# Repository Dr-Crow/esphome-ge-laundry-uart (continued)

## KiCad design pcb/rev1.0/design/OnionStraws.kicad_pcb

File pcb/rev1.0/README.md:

# PCB Rev 1.0

Rev 1.0 is the historical one-input carrier for a generic 38-pin classic ESP32 development board and an external buck module. It added resistor positions for inverted GEA2 serial signaling. Current C3 firmware profiles do not match this board's UART pins.

[Editable source](design/) has been restored from exact public commit `87984047ee029efb83bf9947dc21818fd18e39b3` and cleaned with project-local source definitions and explicit external-supply ERC modelling. The original pin/net groups, parts, routes, positions, outline and holes are retained. Only connector silk outside the board has a physical geometry edit. Genuine KiCad 9.0.9 reports zero ERC errors/warnings after explicit faithful VCC presentation, and zero DRC/parity/unconnected findings.

Read the [native source review](validation/NATIVE-REVIEW.md), [schematic](validation/schematic.pdf), [board views](validation/views/), and [source/export proof](validation/native-kicad-9.0.9/preservation-proof.json). The [current review CAM](review-manufacturing/) is separate from the byte-preserved [original Gerber archive](manufacturing/GERBER-OnionStraws-rev1.0.zip). No supplier BOM or CPL was present in the original package; none has been invented.

This historical source cleanup does not establish electrical/appliance qualification or manufacturing readiness. Original supply, protection, supervisor, buck-module, thermal and physical gates remain open. Classic ESP32 firmware is handled separately.

[Back to the PCB revision index](../README.md)

[Standalone candidate scope and release boundaries](STANDALONE-REVIEW.md).

## Current schematic presentation

[Schematic normalization](validation/erc-normalization/integration-updates.json) resolves the former alias warnings with explicit faithful power presentation. Native KiCad 9.0.9 now reports zero errors/warnings/unconnected/parity. Original physical architecture, PCB/CAM, firmware and pin memberships remain; power/module/procurement/assembly/physical gates are still open. Earlier source/independent receipts are frozen historical evidence.

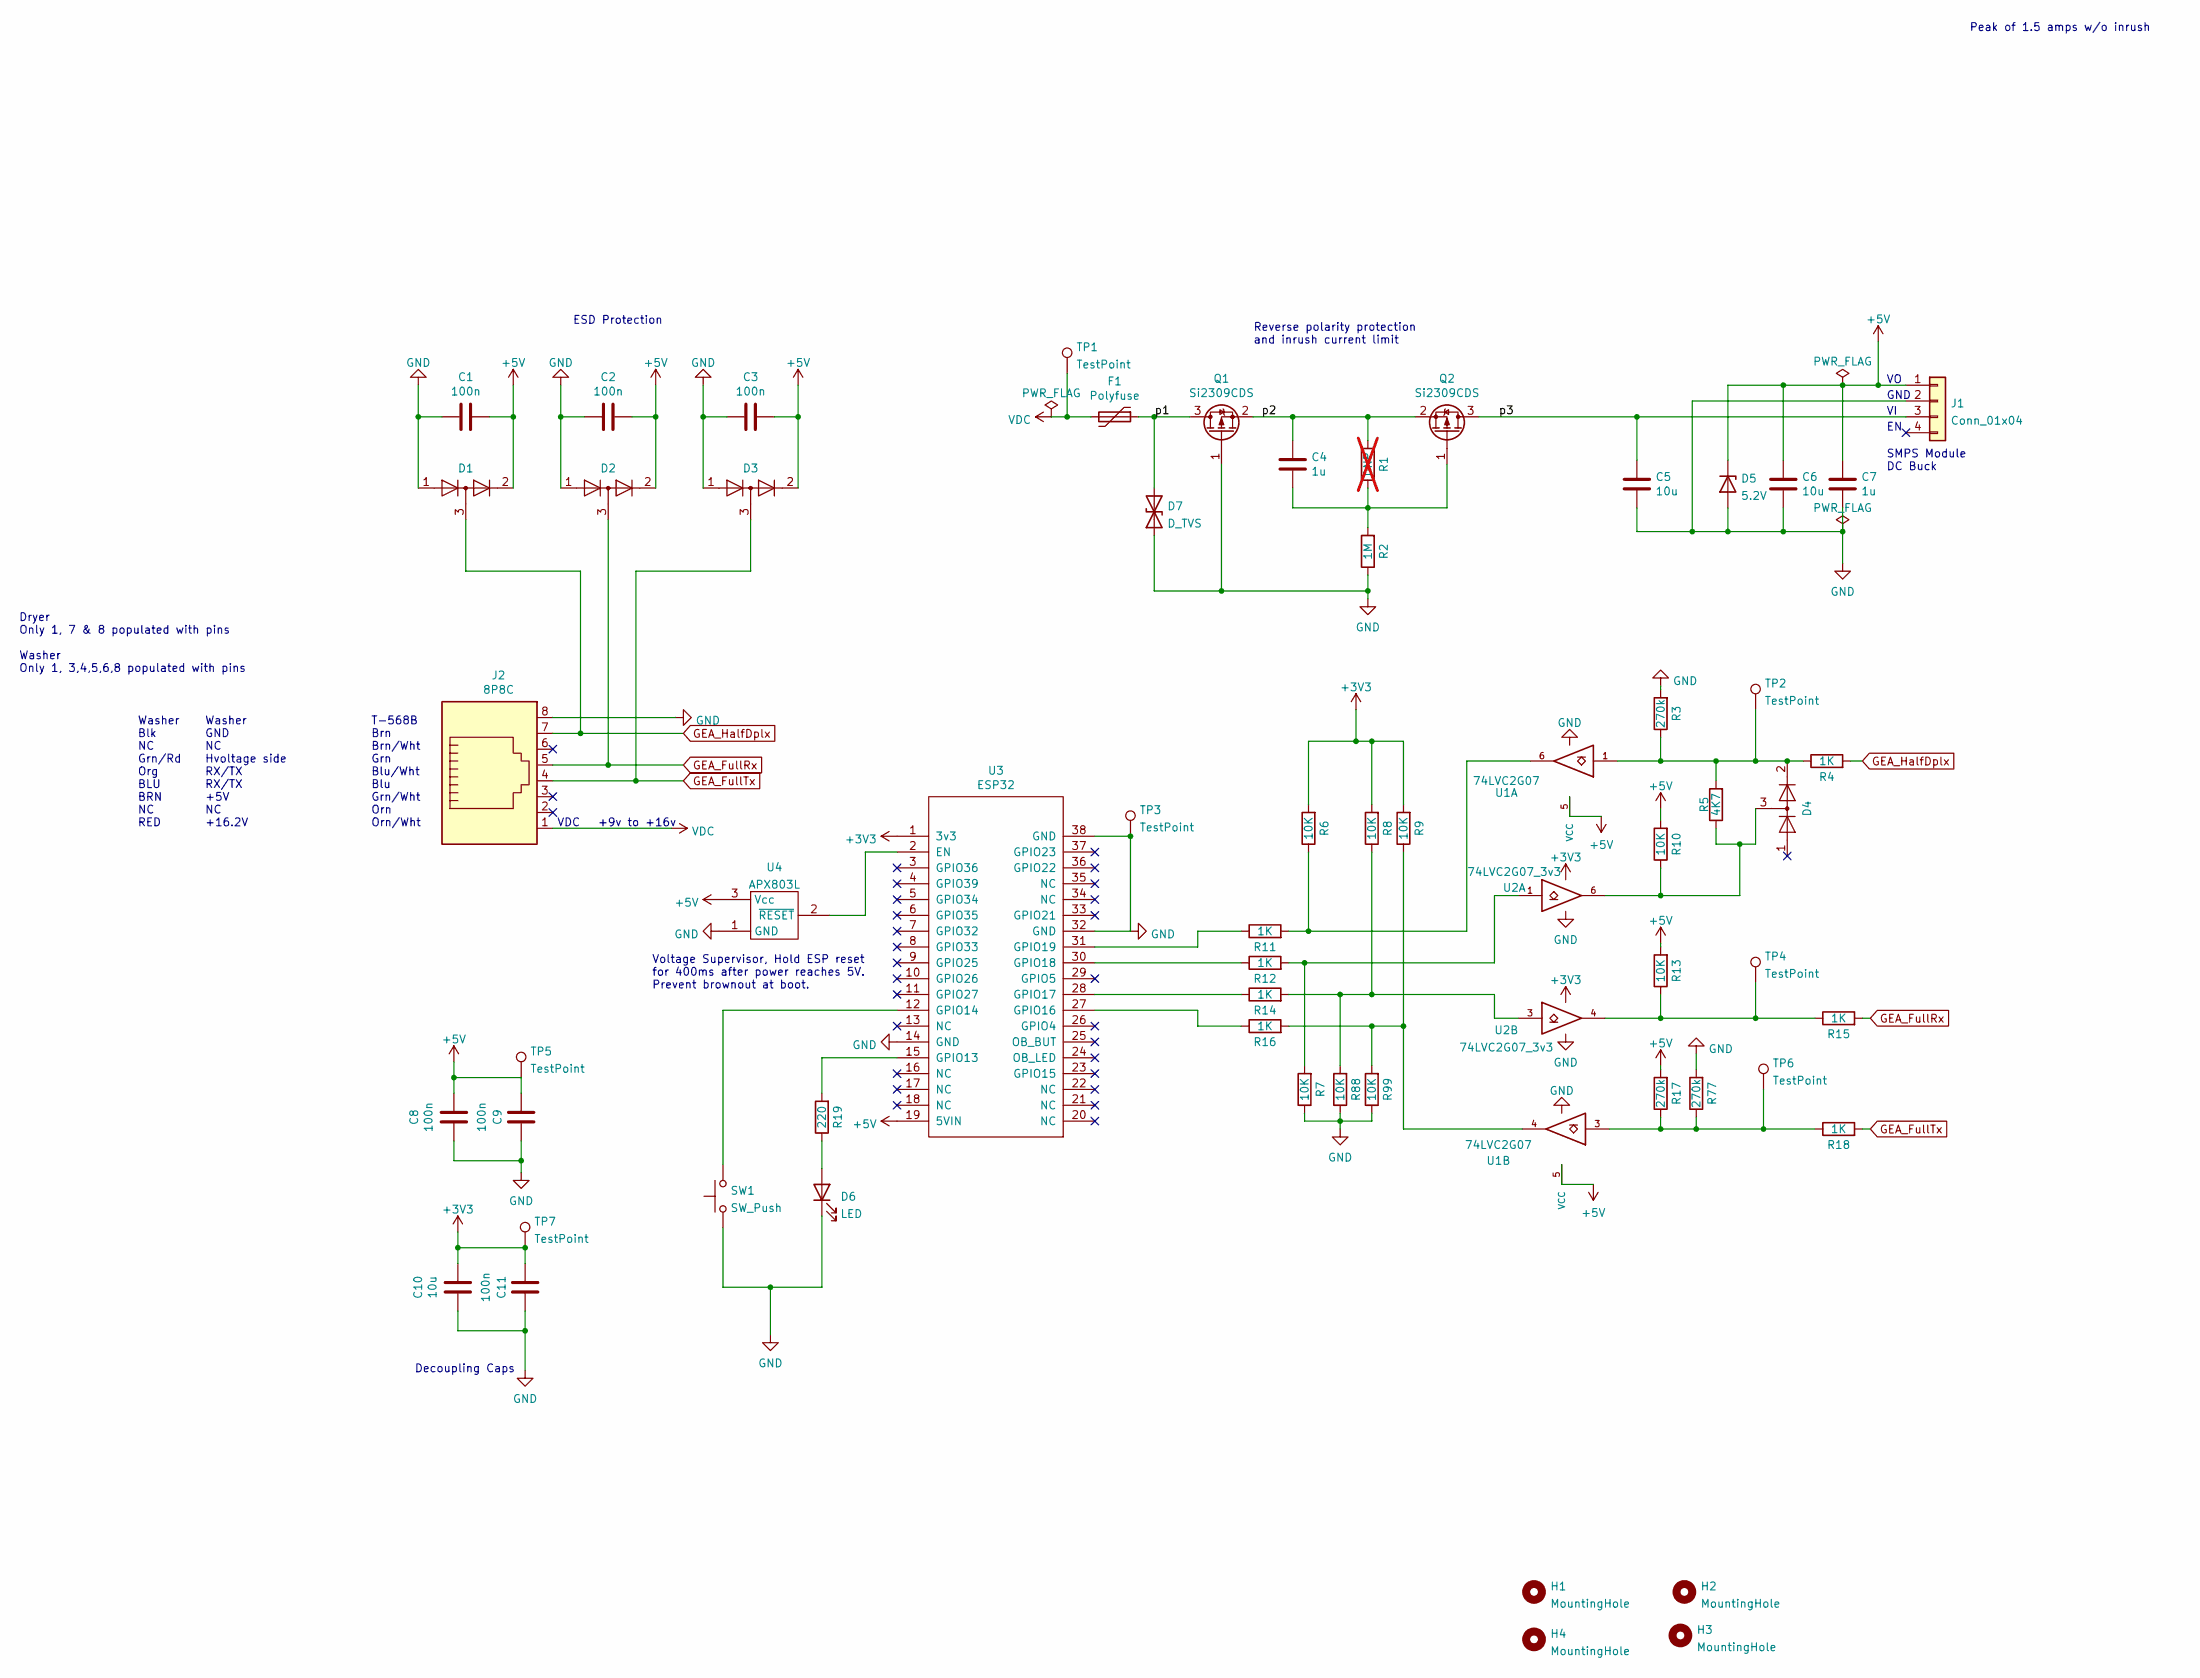
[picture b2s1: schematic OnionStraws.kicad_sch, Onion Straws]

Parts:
C1: 100n; C1_CP_EIA-1608-10_AVX-L
C2: 100n; C2_CP_EIA-1608-10_AVX-L
C3: 100n; C3_CP_EIA-1608-10_AVX-L
C4: 1u; C4_C_0805_2012Metric
C5: 10u; C5_C_0805_2012Metric
C6: 10u; C6_C_0805_2012Metric
C7: 1u; C7_C_0805_2012Metric
C8: 100n; C8_C_0805_2012Metric
C9: 100n; C9_C_0805_2012Metric
C10: 10u; C10_C_0805_2012Metric
C11: 100n; C11_C_0805_2012Metric
D1: BAV99; D1_SOT-23
D2: BAV99; D2_SOT-23
D3: BAV99; D3_SOT-23
D4: BAV99; D4_SOT-23
D5: 5.2V; D5_D_SOD-123
D6: LED; D6_LED_D5.0mm
D7: D_TVS; D7_D_SMA
F1: Polyfuse; F1_R_1210_3225Metric_Pad1.30x2.65mm_HandSolder
H1: MountingHole; H1_MountingHole_3.2mm_M3_DIN965
H2: MountingHole; H2_MountingHole_3.2mm_M3_DIN965
H3: MountingHole; H3_MountingHole_3.2mm_M3_DIN965
H4: MountingHole; H4_MountingHole_3.2mm_M3_DIN965
J1: Conn_01x04; J1_PinHeader_1x04_P2.54mm_Horizontal
J2: 8P8C; J2_RJ45_Amphenol_54602-x08_Horizontal
Q1: Si2309CDS; Q1_SOT-23
Q2: Si2309CDS; Q2_SOT-23
R1: DNP; R1_R_0805_2012Metric; not fitted
R2: 1M; R2_R_0805_2012Metric
R3: 270k; R3_R_0805_2012Metric
R4: 1K; R4_R_0805_2012Metric
R5: 4K7; R5_R_0805_2012Metric
R6: 10K; R6_R_0805_2012Metric
R7: 10K; R7_R_0805_2012Metric
R8: 10K; R8_R_0805_2012Metric
R9: 10K; R9_R_0805_2012Metric
R10: 10K; R10_R_0805_2012Metric
R11: 1K; R11_R_0805_2012Metric
R12: 1K; R12_R_0805_2012Metric
R13: 10K; R13_R_0805_2012Metric
R14: 1K; R14_R_0805_2012Metric
R15: 1K; R15_R_0805_2012Metric
R16: 1K; R16_R_0805_2012Metric
R17: 270k; R17_R_0805_2012Metric
R18: 1K; R18_R_0805_2012Metric
R19: 220; R19_R_0805_2012Metric
R77: 270k; R77_R_0805_2012Metric
R88: 10K; R88_R_0805_2012Metric
R99: 10K; R99_R_0805_2012Metric
SW1: SW_Push; SW1_SW_PUSH_6mm_H13mm
TP1: TestPoint; TP1_TestPoint_THTPad_D2.5mm_Drill1.2mm
TP2: TestPoint; TP2_TestPoint_THTPad_D2.5mm_Drill1.2mm
TP3: TestPoint; TP3_TestPoint_THTPad_D2.5mm_Drill1.2mm
TP4: TestPoint; TP4_TestPoint_THTPad_D2.5mm_Drill1.2mm
TP5: TestPoint; TP5_TestPoint_THTPad_D2.5mm_Drill1.2mm
TP6: TestPoint; TP6_TestPoint_THTPad_D2.5mm_Drill1.2mm
TP7: TestPoint; TP7_TestPoint_THTPad_D2.5mm_Drill1.2mm
U1: 74LVC2G07; U1_SOT-23-6
U2: 74LVC2G07_3v3; U2_SOT-23-6
U3: ESP32; U3_DIP-38_900_ELL
U4: APX803L; U4_SOT-23

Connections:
+3V3: C10.1, C11.2, R6.2, R8.2, R9.2, TP7.1, U2.5 (+3V3), U3.1 (3v3)
+5V: C1.1, C2.1, C3.1, C6.1, C7.1, C8.1, C9.2, D1.2 (A), D2.2 (A), D3.2 (A), D5.1 (K), J1.1, R10.2, R13.2, R17.2, TP5.1, U1.5 (VCC), U3.19 (5VIN), U4.3 (Vcc)
/p1: D7.2 (A2), F1.1, Q1.3 (D)
/p2: C4.1, Q1.2 (S), Q2.2 (S), R1.2
/p3: C5.1, J1.3, Q2.3 (D)
GEA_FullRx: D2.3 (K), J2.5, R15.2
GEA_FullTx: D3.3 (K), J2.4, R18.2
GEA_HalfDplx: D1.3 (K), J2.7, R4.2
GND: C1.2, C2.2, C3.2, C5.2, C6.2, C7.2, C8.2, C9.1, C10.2, C11.1, D1.1 (K), D2.1 (K), D3.1 (K), D5.2 (A), D6.1 (K), D7.1 (A1), J1.2, J2.8, Q1.1 (G), R2.1, R3.2, R7.1, R77.2, R88.1, R99.1, SW1.1, TP3.1, U1.2 (GND), U2.2 (GND), U3.14 (GND), U3.32 (GND), U3.38 (GND), U4.1 (GND)
unnamed: D4.2 (A), R3.1, R4.1, R5.2, TP2.1, U1.1
unnamed: D4.3 (K), R5.1, R10.1, U2.6
unnamed: D6.2 (A), R19.1
unnamed: C4.2, Q2.1 (G), R1.1, R2.2
unnamed: R6.1, R11.2, U1.6
unnamed: R7.2, R12.2, U2.1
unnamed: R13.1, R15.1, TP4.1, U2.4
unnamed: R8.1, R14.2, R88.2, U2.3
unnamed: R9.1, R16.2, R99.2, U1.4
unnamed: R17.1, R18.1, R77.1, TP6.1, U1.3
unnamed: U3.2 (EN), U4.2 (~RESET)
unnamed: R19.2, U3.15 (GPIO13)
unnamed: SW1.2, U3.12 (GPIO14)
unnamed: R16.1, U3.27 (GPIO16)
unnamed: R14.1, U3.28 (GPIO17)
unnamed: R12.1, U3.30 (GPIO18)
unnamed: R11.1, U3.31 (GPIO19)
VDC: F1.2, J2.1, TP1.1

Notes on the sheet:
Voltage Supervisor, Hold ESP reset for 400ms after power reaches 5V. Prevent brownout at boot.
Washer Blk NC Grn/Rd Org BLU BRN NC RED
Reverse polarity protection and inrush current limit
Dryer Only 1, 7 & 8 populated with pins Washer Only 1, 3,4,5,6,8 populated with pins
Washer GND NC Hvoltage side RX/TX RX/TX +5V NC +16.2V
Decoupling Caps
Peak of 1.5 amps w/o inrush
ESD Protection
T-568B Brn Brn/Wht Grn Blu/Wht Blu Grn/Wht Orn Orn/Wht
GND
SMPS Module DC Buck
VDC +9v to +16v

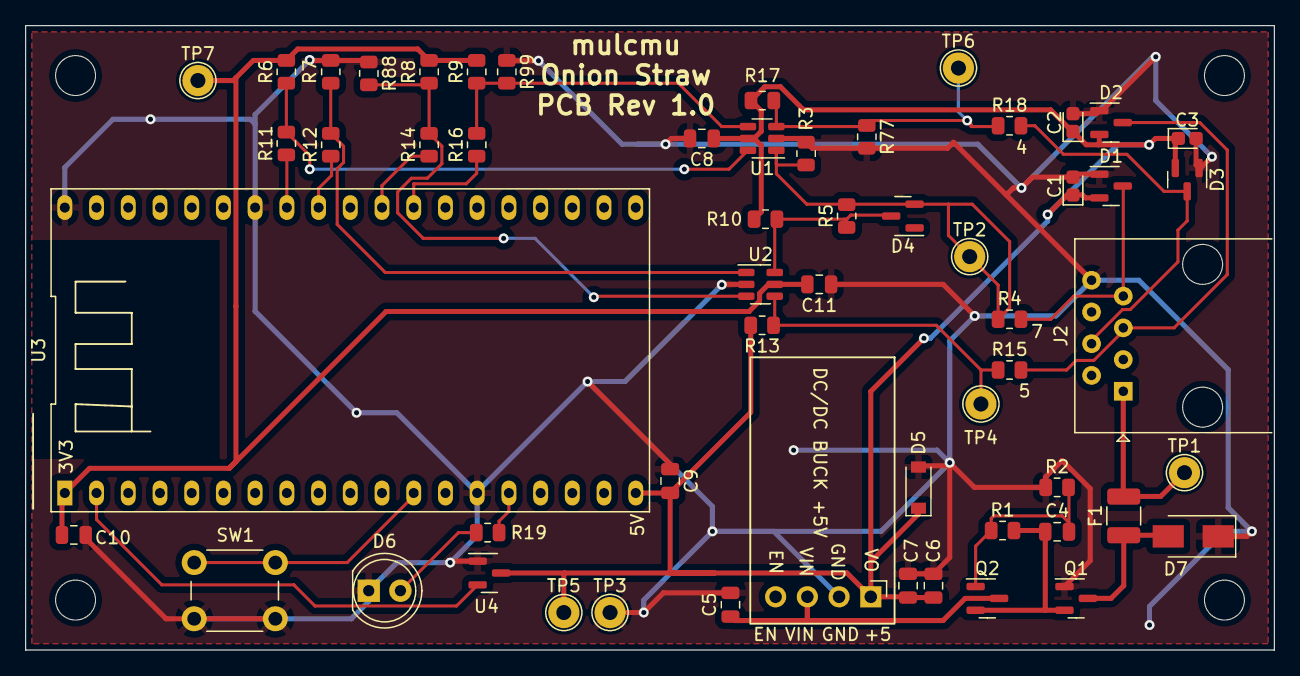
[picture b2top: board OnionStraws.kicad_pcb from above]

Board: 2 copper layers, 100.0 x 50.0 mm, 61 parts (0 on the bottom side), 27 nets.
